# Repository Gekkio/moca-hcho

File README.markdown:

<!--
SPDX-FileCopyrightText: 2021-2022 Joonas Javanainen <joonas.javanainen@gmail.com>

SPDX-License-Identifier: CC0-1.0
-->

# moca-hcho: Bluetooth 5 BLE formaldehyde/temperature/humidity sensor beacon

moca-hcho is a simple Bluetooth Low Energy sensor beacon that uses a [Sensirion SFA30 Formaldehyde Sensor Module](https://www.sensirion.com/en/environmental-sensors/formaldehyde-sensor-sfa30/) to sense formaldehyde/temperature/humidity.
This information is measured and sent periodically using Bluetooth BLE advertisements, which can be received by any Bluetooth 4.0+ device within range.

Overview:

* Enclosure: Hammond 1551V4WH vented sensor enclosure (wall-mountable)
* Sensor: Sensirion SFA30 Formaldehyde sensor module
* Microcontroller: Fanstel BT832 Bluetooth module with Nordic nRF52832
* Power supply: external +5V power supply
* Firmware (less than 1 kLOC) is written in [Rust](https://www.rust-lang.org/) using the [Embassy embedded async/await framework](https://github.com/embassy-rs/embassy)
* Data is sent periodically using Bluetooth BLE advertisements that are very simple to send and receive
* **Not FCC/Bluetooth/etc certified/qualified** but a "best effort" -style approach is used by using qualified BT832 module with integrated antenna + qualified Nordic S112 SoftDevice Bluetooth stack.

## Potential future improvements

* Tidy up the code...currently the code is very crude and could use a lot of polish and some tests should be written
* Improve environmental coupling of the sensor. The vented enclosure works fine, but SFA30 Design-In Guide suggests even better environmental coupling options
* Add encryption. Unencrypted advertisements can be read or spoofed by anyone
* Re-evaluate the feasibility of using a battery

## License

Hardware is licensed under Creative Commons Attribution 4.0 International.

Firmware is licensed under either of

 * Apache License, Version 2.0, ([LICENSE-APACHE](LICENSE-APACHE) or http://www.apache.org/licenses/LICENSE-2.0)
 * MIT license ([LICENSE-MIT](LICENSE-MIT) or http://opensource.org/licenses/MIT)

at your option.

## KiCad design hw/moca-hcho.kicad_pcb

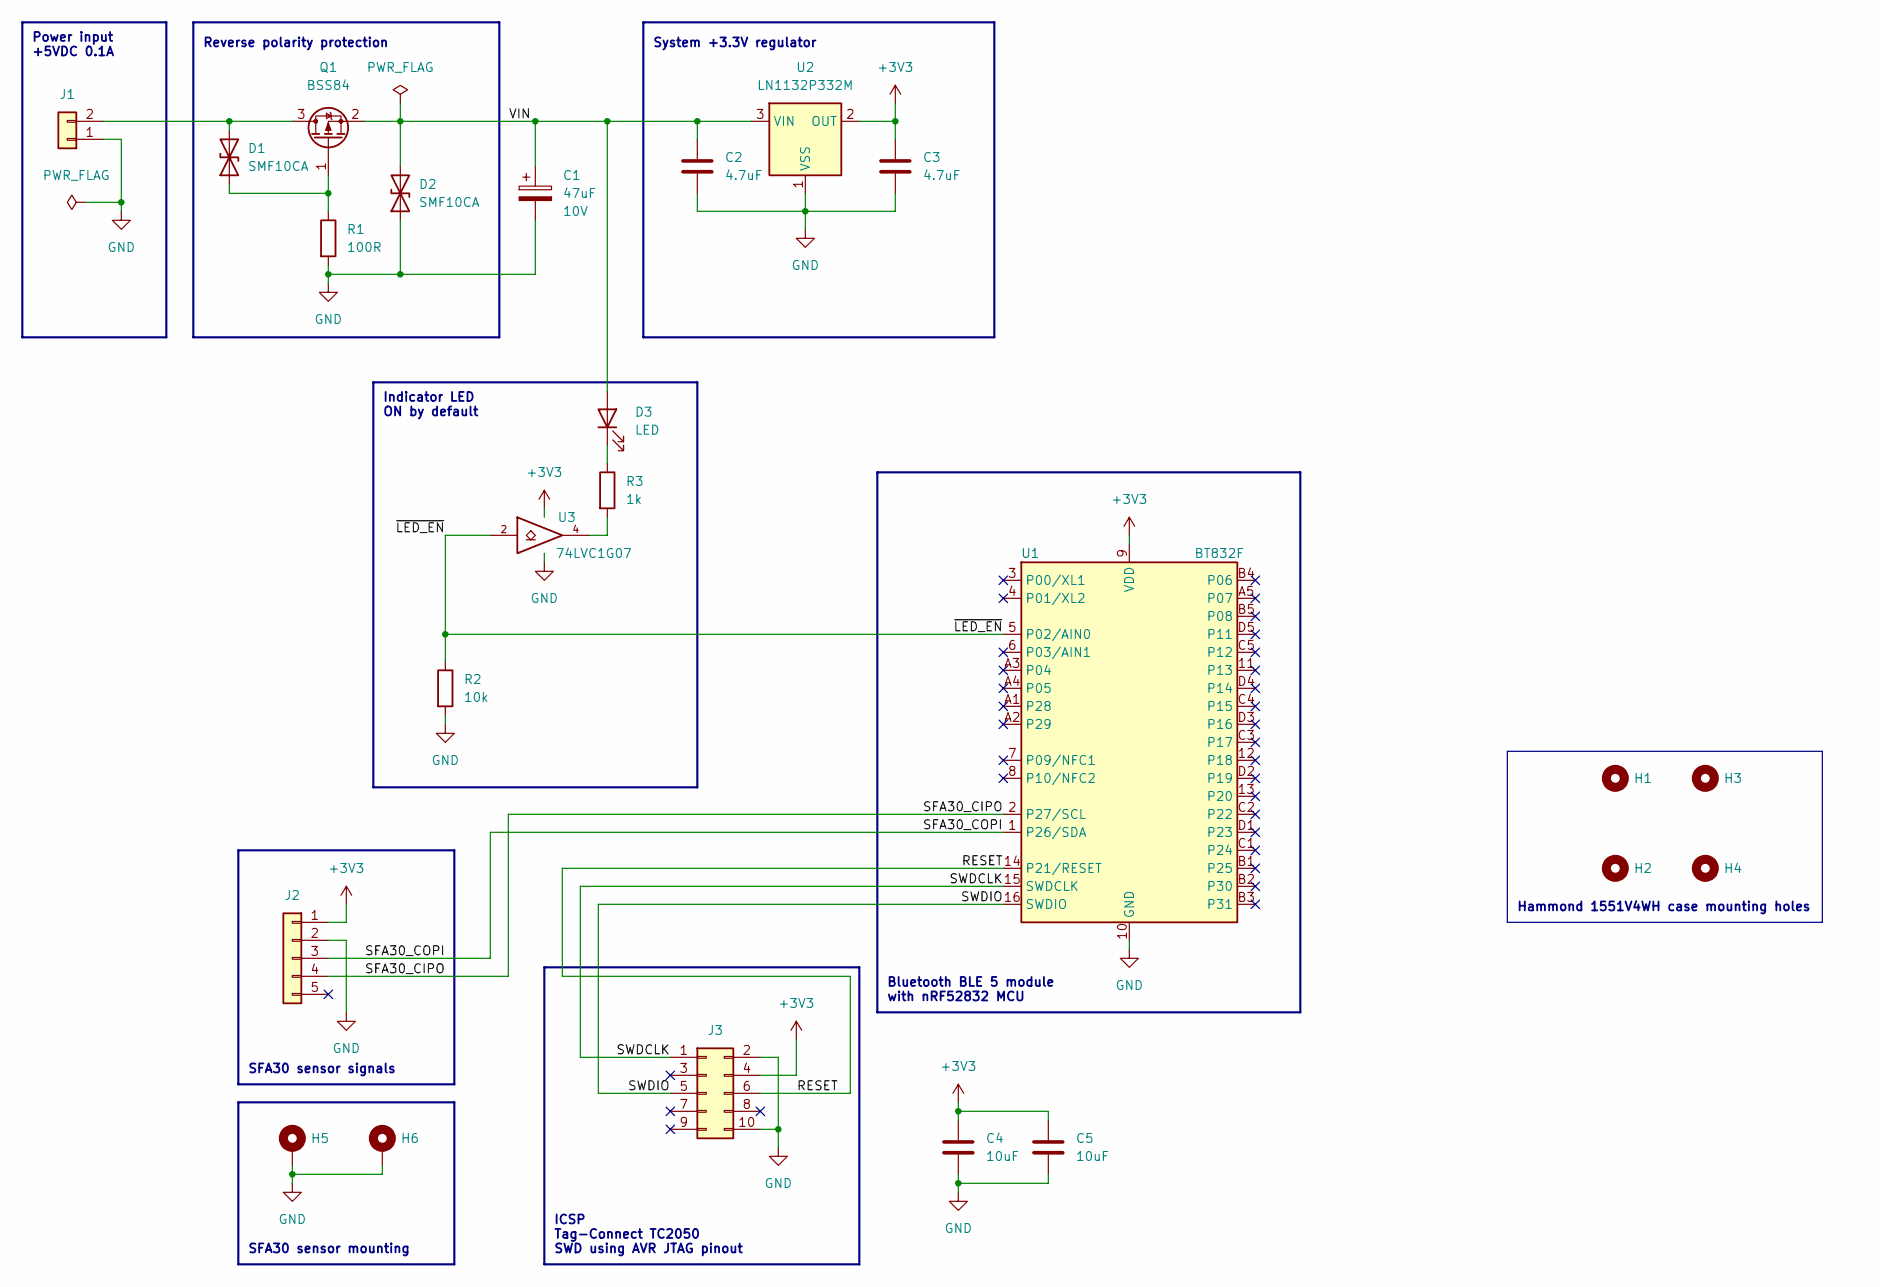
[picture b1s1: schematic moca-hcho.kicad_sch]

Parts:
C1: 47uF; CP_Elec_5x5.8; Rating 10V
C2, C3: 4.7uF; C_0805_2012Metric
C4, C5: 10uF; C_1206_3216Metric
D1, D2: SMF10CA; D_SOD-123F
D3: LED; LED_D3.0mm
H1, H2, H3, H4: DNP; MountingHole_2.5mm
H5, H6: DNP; MountingHole_2.7mm_M2.5_DIN965_Pad
J1: DNP; SolderWire-0.25sqmm_1x02_P4.2mm_D0.65mm_OD1.7mm_Relief
J2: DNP; SolderWire-0.15sqmm_1x05_P4mm_D0.5mm_OD1.5mm
J3: DNP; Tag-Connect_TC2050-IDC-NL_2x05_P1.27mm_Vertical
Q1: BSS84; SOT-23
R1: 100R; R_0805_2012Metric
R2: 10k; R_0805_2012Metric
R3: 1k; R_0805_2012Metric
U1: BT832F; Fanstel_BT832F
U2: LN1132P332M; SOT-23
U3: 74LVC1G07; SOT-353_SC-70-5

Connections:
+3V3: C3.1, C4.1, C5.1, J2.1, J3.4, U1.9 (VDD), U2.2 (OUT), U3.5 (VCC)
/RESET: J3.6, U1.14 (P21/RESET)
/SFA30_CIPO: J2.4, U1.2 (P27/SCL)
/SFA30_COPI: J2.3, U1.1 (P26/SDA)
/SWDCLK: J3.1, U1.15 (SWDCLK)
/SWDIO: J3.5, U1.16 (SWDIO)
/VIN: C1.1, C2.1, D2.2 (A2), D3.2 (A), Q1.2 (S), U2.3 (VIN)
/~LED_EN: R2.1, U1.5 (P02/AIN0), U3.2
GND: C1.2, C2.2, C3.2, C4.2, C5.2, D2.1 (A1), H5.1, H6.1, J1.1, J2.2, J3.2, J3.10, R1.2, R2.2, U1.10 (GND), U1.A0 (GND), U1.B0 (GND), U1.C0 (GND), U1.D0 (GND), U2.1 (VSS), U3.3 (GND)
unnamed: D1.1 (A1), Q1.1 (G), R1.1
unnamed: D1.2 (A2), J1.2, Q1.3 (D)
unnamed: D3.1 (K), R3.1
unnamed: R3.2, U3.4

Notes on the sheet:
System +3.3V regulator
Indicator LED ON by default
SFA30 sensor mounting
Reverse polarity protection
SFA30 sensor signals
Power input +5VDC 0.1A
Bluetooth BLE 5 module with nRF52832 MCU
Hammond 1551V4WH case mounting holes
ICSP Tag-Connect TC2050 SWD using AVR JTAG pinout

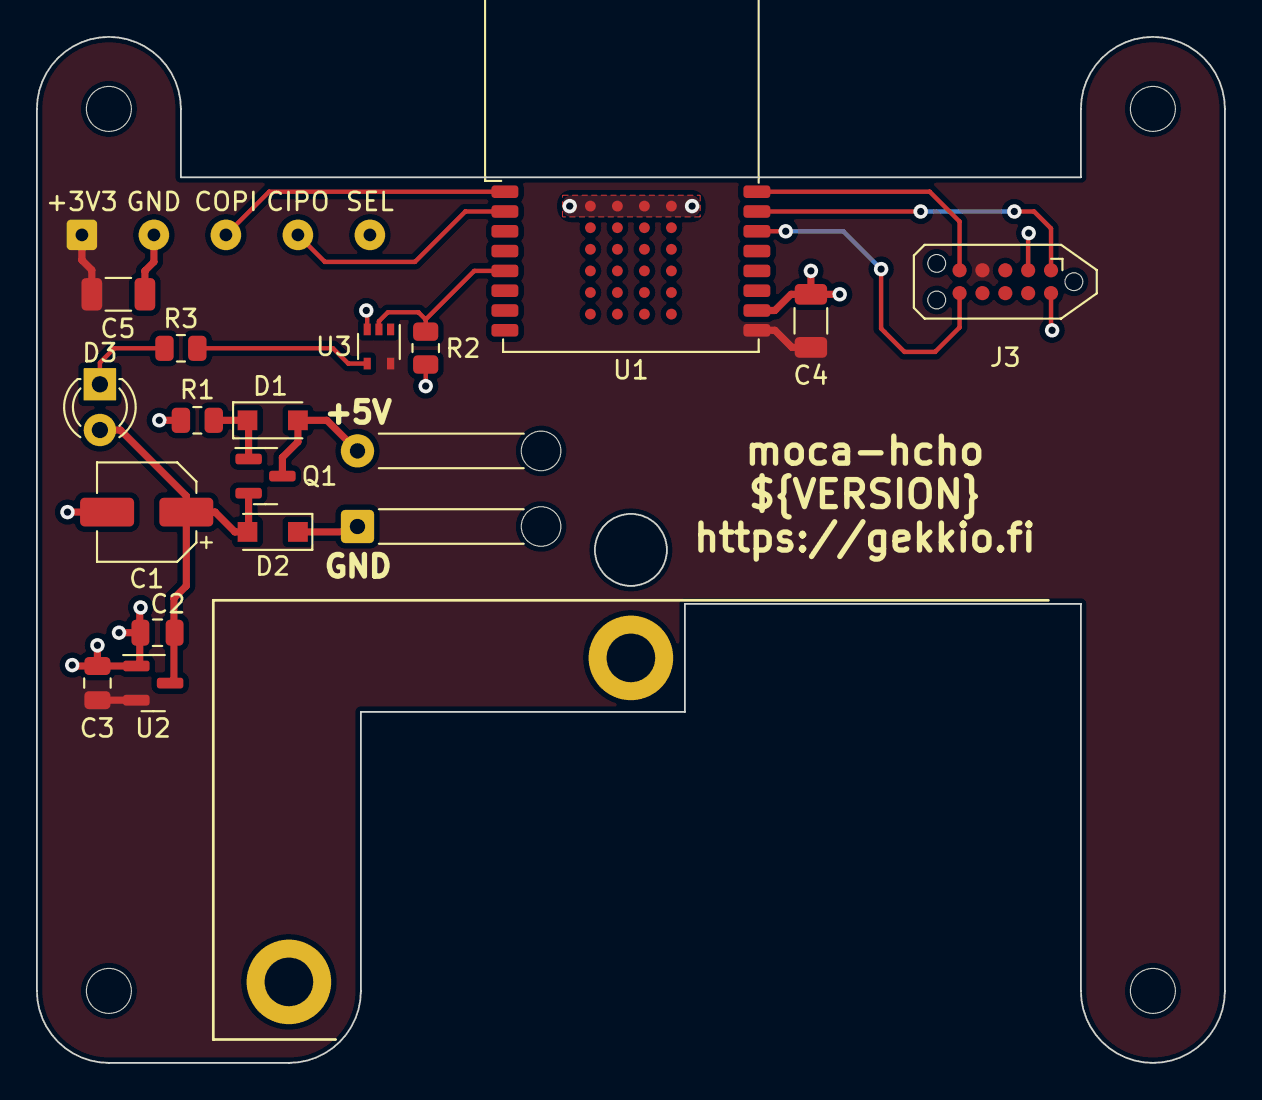
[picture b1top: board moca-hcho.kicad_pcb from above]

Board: 2 copper layers, 66.0 x 57.0 mm, 24 parts (0 on the bottom side), 13 nets.

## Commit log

2022-01-01 Improve README
